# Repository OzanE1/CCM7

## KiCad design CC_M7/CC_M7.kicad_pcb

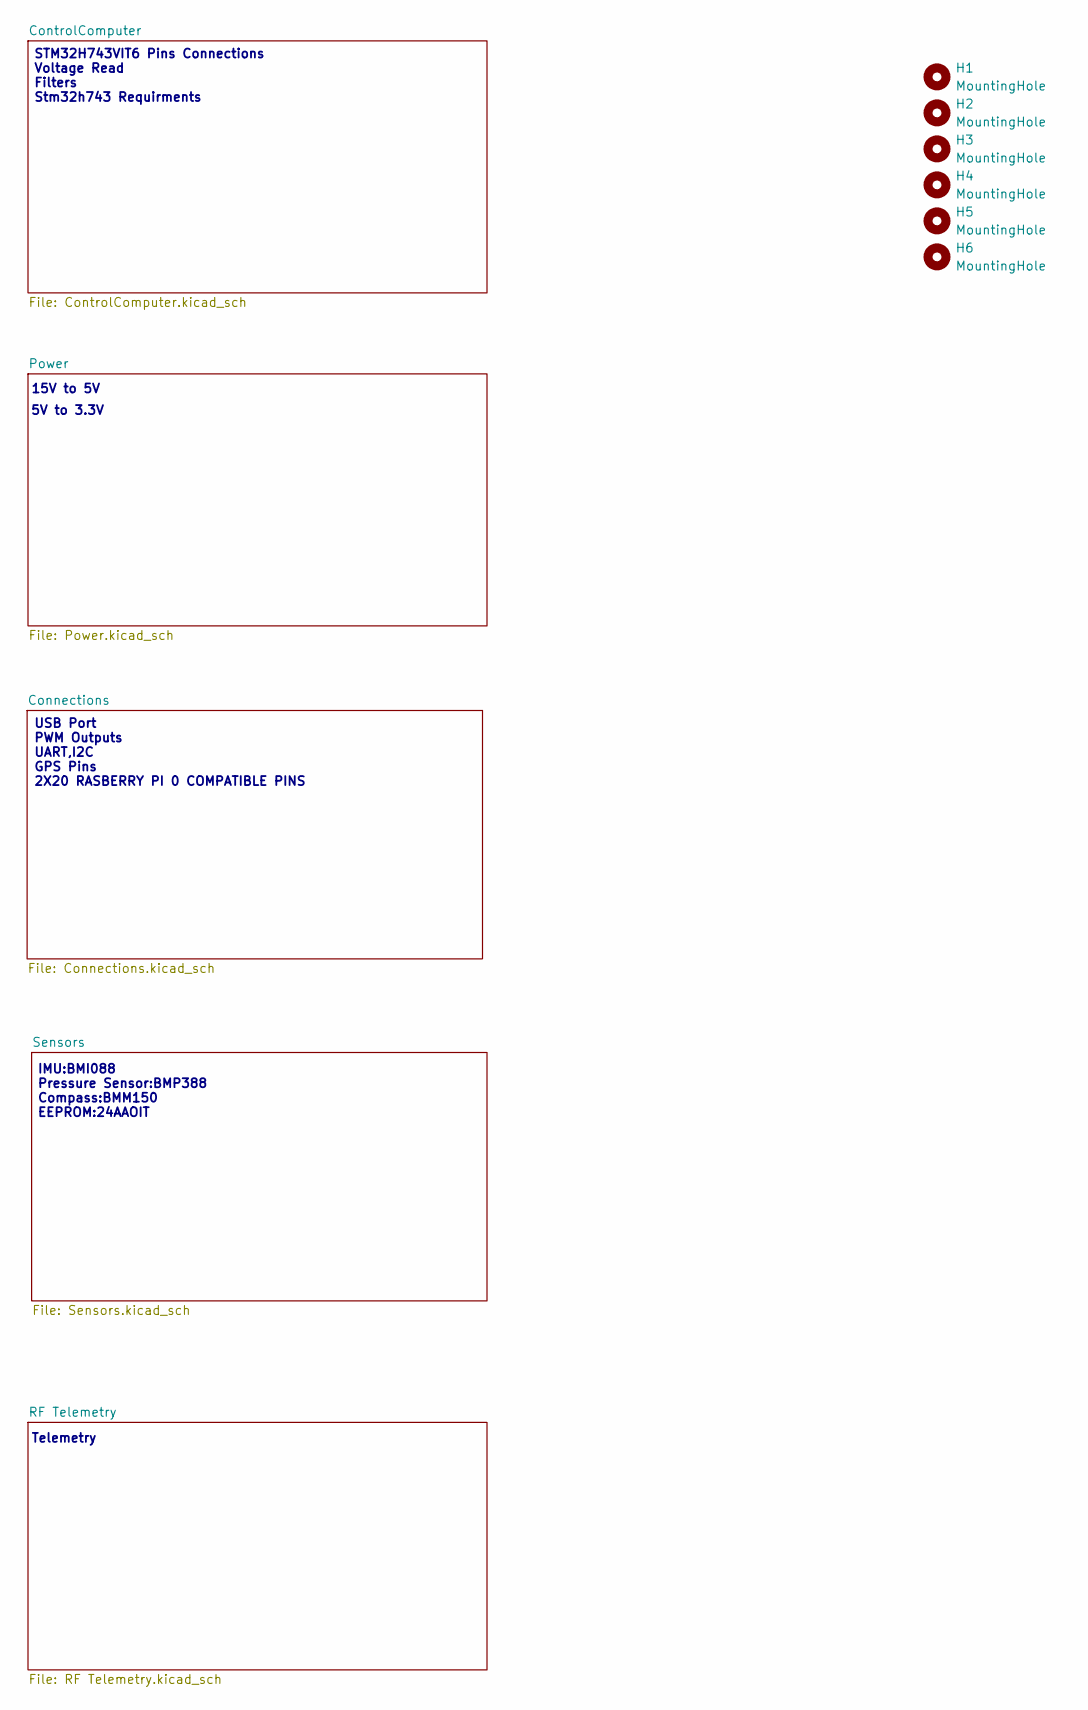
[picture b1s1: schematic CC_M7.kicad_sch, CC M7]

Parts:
H1, H2, H3, H4, H5, H6: MountingHole; MountingHole_3.2mm_M3_ISO14580_Pad

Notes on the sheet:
15V to 5V
5V to 3.3V
USB Port PWM Outputs UART,I2C GPS Pins 2X20 RASBERRY PI 0 COMPATIBLE PINS
Telemetry
STM32H743VIT6 Pins Connections Voltage Read Filters Stm32h743 Requirments
IMU:BMI088 Pressure Sensor:BMP388 Compass:BMM150 EEPROM:24AAOIT

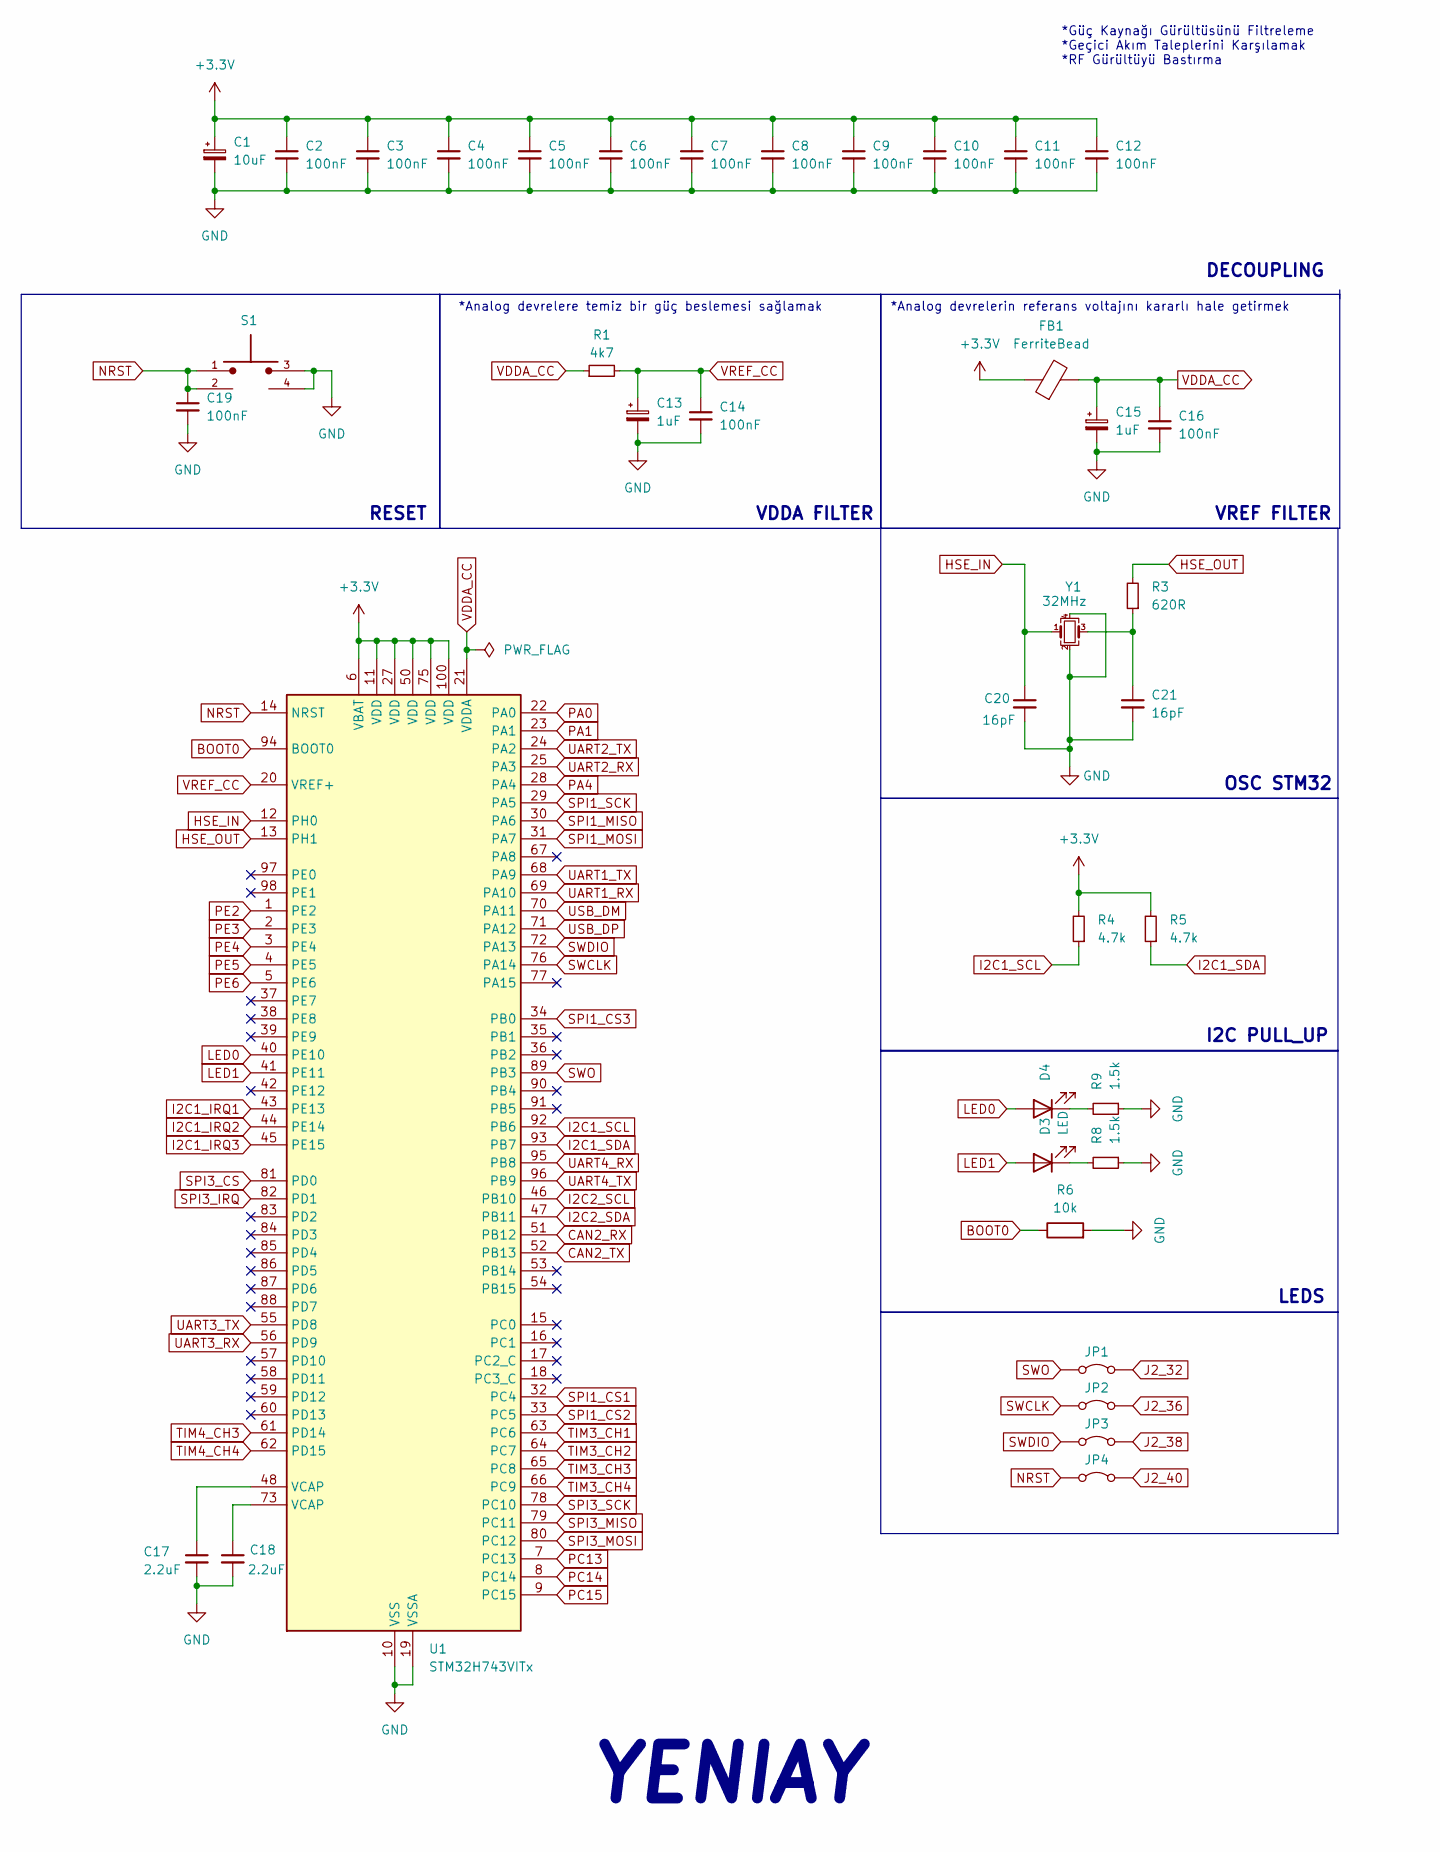
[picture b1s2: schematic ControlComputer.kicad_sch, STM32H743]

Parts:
C1: 10uF; C_0603_1608Metric
C2, C3, C4, C5, C6, C7, C8, C9, C10, C11, C12, C14, C16, C19: 100nF; C_0603_1608Metric
C13, C15: 1uF; C_0603_1608Metric
C17, C18: 2.2uF; C_0603_1608Metric
C20, C21: 16pF; C_0603_1608Metric
D3, D4: LED; LED_0603_1608Metric
FB1: FerriteBead; L_0603_1608Metric
JP1, JP2, JP3, JP4: SWDIO; jmpertest
R1: 4k7; R_0603_1608Metric
R3: 620R; R_0603_1608Metric
R4, R5: 4.7k; R_0603_1608Metric
R6: 10k; R_0603_1608Metric
R8, R9: 1.5k; R_0603_1608Metric
S1: SKRPABE010; SW_SKRPABE010
U1: STM32H743VITx; LQFP-100_14x14mm_P0.5mm
Y1: 32MHz; Crystal_SMD_3225-4Pin_3.2x2.5mm

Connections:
+3.3V: C1.1, C2.1, C3.1, C4.1, C5.1, C6.1, C7.1, C8.1, C9.1, C10.1, C11.1, C12.1, FB1.1, R4.2, R5.2, U1.6 (VBAT), U1.11 (VDD), U1.27 (VDD), U1.50 (VDD), U1.75 (VDD), U1.100 (VDD); also elsewhere on the board
BOOT0: R6.1, U1.94 (BOOT0)
CAN2_RX: U1.51 (PB12); also elsewhere on the board
CAN2_TX: U1.52 (PB13); also elsewhere on the board
GND: C1.2, C2.2, C3.2, C4.2, C5.2, C6.2, C7.2, C8.2, C9.2, C10.2, C11.2, C12.2, C13.2, C14.2, C15.2, C16.2, C17.2, C18.2, C19.2, C20.2, C21.2, R6.2, R8.1, R9.1, S1.3, S1.4, U1.10 (VSS), U1.19 (VSSA), U1.26 (VSS), U1.49 (VSS), U1.74 (VSS), U1.99 (VSS), Y1.2, Y1.4; also elsewhere on the board
HSE_IN: C20.1, U1.12 (PH0), Y1.1
HSE_OUT: R3.2, U1.13 (PH1)
I2C1_IRQ1: U1.43 (PE13); also elsewhere on the board
I2C1_IRQ2: U1.44 (PE14); also elsewhere on the board
I2C1_IRQ3: U1.45 (PE15); also elsewhere on the board
I2C1_SCL: R4.1, U1.92 (PB6); also elsewhere on the board
I2C1_SDA: R5.1, U1.93 (PB7); also elsewhere on the board
I2C2_SCL: U1.46 (PB10); also elsewhere on the board
I2C2_SDA: U1.47 (PB11); also elsewhere on the board
J2_32: JP1.2 (B); also elsewhere on the board
J2_36: JP2.2 (B); also elsewhere on the board
J2_38: JP3.2 (B); also elsewhere on the board
J2_40: JP4.2 (B); also elsewhere on the board
LED0: D4.2 (A), U1.40 (PE10)
LED1: D3.2 (A), U1.41 (PE11)
NRST: C19.1, JP4.1 (A), S1.1, S1.2, U1.14 (NRST)
unnamed: C17.1, U1.48 (VCAP)
unnamed: C18.1, U1.73 (VCAP)
unnamed: C21.1, R3.1, Y1.3
unnamed: D3.1 (K), R8.2
unnamed: D4.1 (K), R9.2
PA0: U1.22 (PA0); also elsewhere on the board
PA1: U1.23 (PA1); also elsewhere on the board
PA4: U1.28 (PA4); also elsewhere on the board
PC13: U1.7 (PC13); also elsewhere on the board
PC14: U1.8 (PC14); also elsewhere on the board
PC15: U1.9 (PC15); also elsewhere on the board
PE2: U1.1 (PE2); also elsewhere on the board
PE3: U1.2 (PE3); also elsewhere on the board
PE4: U1.3 (PE4); also elsewhere on the board
PE5: U1.4 (PE5); also elsewhere on the board
PE6: U1.5 (PE6); also elsewhere on the board
SPI1_CS1: U1.32 (PC4); also elsewhere on the board
SPI1_CS2: U1.33 (PC5); also elsewhere on the board
SPI1_CS3: U1.34 (PB0); also elsewhere on the board
SPI1_MISO: U1.30 (PA6); also elsewhere on the board
SPI1_MOSI: U1.31 (PA7); also elsewhere on the board
SPI1_SCK: U1.29 (PA5); also elsewhere on the board
SPI3_CS: U1.81 (PD0); also elsewhere on the board
SPI3_IRQ: U1.82 (PD1); also elsewhere on the board
SPI3_MISO: U1.79 (PC11); also elsewhere on the board
SPI3_MOSI: U1.80 (PC12); also elsewhere on the board
SPI3_SCK: U1.78 (PC10); also elsewhere on the board
SWCLK: JP2.1 (A), U1.76 (PA14)
SWDIO: JP3.1 (A), U1.72 (PA13)
SWO: JP1.1 (A), U1.89 (PB3)
TIM3_CH1: U1.63 (PC6); also elsewhere on the board
TIM3_CH2: U1.64 (PC7); also elsewhere on the board
TIM3_CH3: U1.65 (PC8); also elsewhere on the board
TIM3_CH4: U1.66 (PC9); also elsewhere on the board
TIM4_CH3: U1.61 (PD14); also elsewhere on the board
TIM4_CH4: U1.62 (PD15); also elsewhere on the board
UART1_RX: U1.69 (PA10); also elsewhere on the board
UART1_TX: U1.68 (PA9); also elsewhere on the board
UART2_RX: U1.25 (PA3); also elsewhere on the board
UART2_TX: U1.24 (PA2); also elsewhere on the board
UART3_RX: U1.56 (PD9); also elsewhere on the board
UART3_TX: U1.55 (PD8); also elsewhere on the board
UART4_RX: U1.95 (PB8); also elsewhere on the board
UART4_TX: U1.96 (PB9); also elsewhere on the board
USB_DM: U1.70 (PA11); also elsewhere on the board
USB_DP: U1.71 (PA12); also elsewhere on the board
VDDA_CC: C15.1, C16.1, FB1.2, R1.1, U1.21 (VDDA)
VREF_CC: C13.1, C14.1, R1.2, U1.20 (VREF+)

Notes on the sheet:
*Güç Kaynağı Gürültüsünü Filtreleme *Geçici Akım Taleplerini Karşılamak *RF Gürültüyü Bastırma
*Analog devrelere temiz bir güç beslemesi sağlamak
DECOUPLING
OSC STM32
VREF FILTER
RESET
I2C PULL_UP
*Analog devrelerin referans voltajını kararlı hale getirmek
LEDS
YENIAY
VDDA FILTER

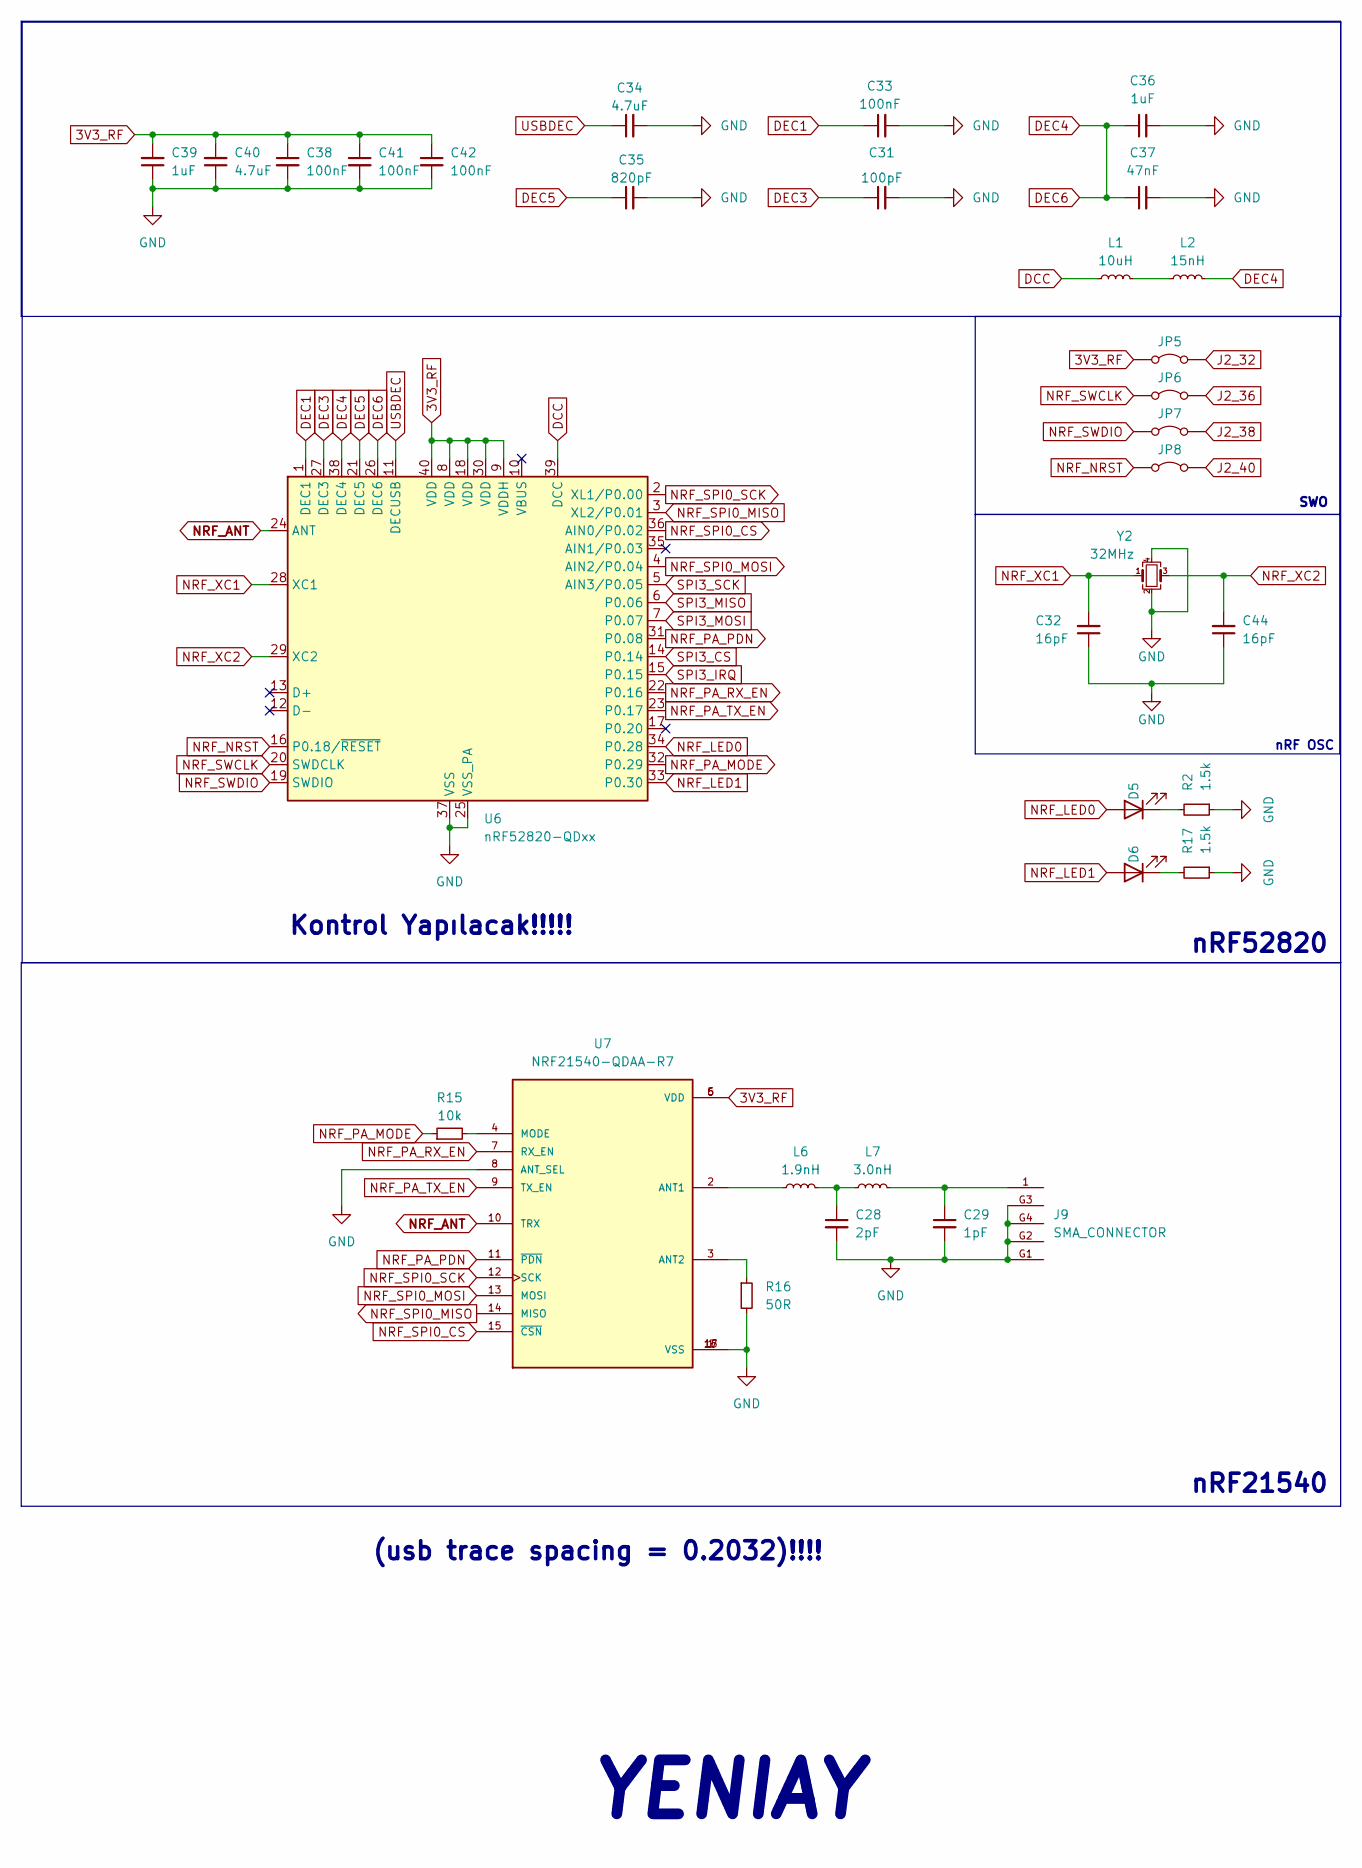
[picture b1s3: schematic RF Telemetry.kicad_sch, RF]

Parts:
C28: 2pF; C_0201_0603Metric
C29: 1pF; C_0201_0603Metric
C31: 100pF; C_0603_1608Metric
C32, C44: 16pF; C_0603_1608Metric
C33, C38, C41, C42: 100nF; C_0603_1608Metric
C34, C40: 4.7uF; C_0603_1608Metric
C35: 820pF; C_0603_1608Metric
C36, C39: 1uF; C_0603_1608Metric
C37: 47nF; C_0603_1608Metric
D5, D6: LED; LED_0603_1608Metric
J9: SMA_CONNECTOR; LPRS_SMA_CONNECTOR; PARTREV 1.3
JP5, JP6, JP7, JP8: SWDIO; jmpertest
L1: 10uH; L_0603_1608Metric
L2: 15nH; L_0603_1608Metric
L6: 1.9nH; L_0201_0603Metric
L7: 3.0nH; L_0201_0603Metric
R2, R17: 1.5k; R_0603_1608Metric
R15: 10k; R_0603_1608Metric
R16: 50R; R_0603_1608Metric
U6: nRF52820-QDxx; QFN-40-1EP_5x5mm_P0.4mm_EP3.6x3.6mm
U7: NRF21540-QDAA-R7; QFN65P400X400X95-17N; PARTREV 1.0
Y2: 32MHz; Crystal_SMD_3225-4Pin_3.2x2.5mm

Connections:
3V3_RF: C38.1, C39.2, C40.2, C41.1, C42.1, JP5.1 (A), U6.8 (VDD), U6.9 (VDDH), U6.18 (VDD), U6.30 (VDD), U6.40 (VDD), U7.5 (VDD), U7.6 (VDD); also elsewhere on the board
DCC: L1.1, U6.39 (DCC)
DEC1: C33.1, U6.1 (DEC1)
DEC3: C31.1, U6.27 (DEC3)
DEC4: C36.1, C37.1, L2.2, U6.26 (DEC6), U6.38 (DEC4)
DEC5: C35.1, U6.21 (DEC5)
GND: C28.2, C29.2, C31.2, C32.1, C33.2, C34.2, C35.2, C36.2, C37.2, C38.2, C39.1, C40.1, C41.2, C42.2, C44.1, J9.G1, J9.G2, J9.G3, J9.G4, R2.1, R16.2, R17.1, U6.25 (VSS_PA), U6.37 (VSS), U6.41 (VSS), U7.1 (VSS), U7.8 (ANT_SEL), U7.16 (VSS), U7.17 (VSS), Y2.2, Y2.4; also elsewhere on the board
J2_32: JP5.2 (B); also elsewhere on the board
J2_36: JP6.2 (B); also elsewhere on the board
J2_38: JP7.2 (B); also elsewhere on the board
J2_40: JP8.2 (B); also elsewhere on the board
NRF_ANT: U6.24 (ANT), U7.10 (TRX)
NRF_LED0: D5.2 (A), U6.34 (P0.28)
NRF_LED1: D6.2 (A), U6.33 (P0.30)
NRF_NRST: JP8.1 (A), U6.16 (P0.18/~RESET)
NRF_PA_MODE: R15.1, U6.32 (P0.29)
NRF_PA_PDN: U6.31 (P0.08), U7.11 (~PDN)
NRF_PA_RX_EN: U6.22 (P0.16), U7.7 (RX_EN)
NRF_PA_TX_EN: U6.23 (P0.17), U7.9 (TX_EN)
NRF_SPI0_CS: U6.36 (AIN0/P0.02), U7.15 (~CSN)
NRF_SPI0_MISO: U6.3 (XL2/P0.01), U7.14 (MISO)
NRF_SPI0_MOSI: U6.4 (AIN2/P0.04), U7.13 (MOSI)
NRF_SPI0_SCK: U6.2 (XL1/P0.00), U7.12 (SCK)
NRF_SWCLK: JP6.1 (A), U6.20 (SWDCLK)
NRF_SWDIO: JP7.1 (A), U6.19 (SWDIO)
NRF_XC1: C32.2, U6.28 (XC1), Y2.1
NRF_XC2: C44.2, U6.29 (XC2), Y2.3
unnamed: C28.1, L6.2, L7.1
unnamed: C29.1, J9.1, L7.2
unnamed: D5.1 (K), R2.2
unnamed: D6.1 (K), R17.2
unnamed: L1.2, L2.1
unnamed: L6.1, U7.2 (ANT1)
unnamed: R16.1, U7.3 (ANT2)
unnamed: R15.2, U7.4 (MODE)
SPI3_CS: U6.14 (P0.14); also elsewhere on the board
SPI3_IRQ: U6.15 (P0.15); also elsewhere on the board
SPI3_MISO: U6.6 (P0.06); also elsewhere on the board
SPI3_MOSI: U6.7 (P0.07); also elsewhere on the board
SPI3_SCK: U6.5 (AIN3/P0.05); also elsewhere on the board
USBDEC: C34.1, U6.11 (DECUSB)

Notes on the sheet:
Kontrol Yapılacak!!!!!
(usb trace spacing = 0.2032)!!!!
nRF21540
nRF52820
YENIAY
nRF OSC
SWO

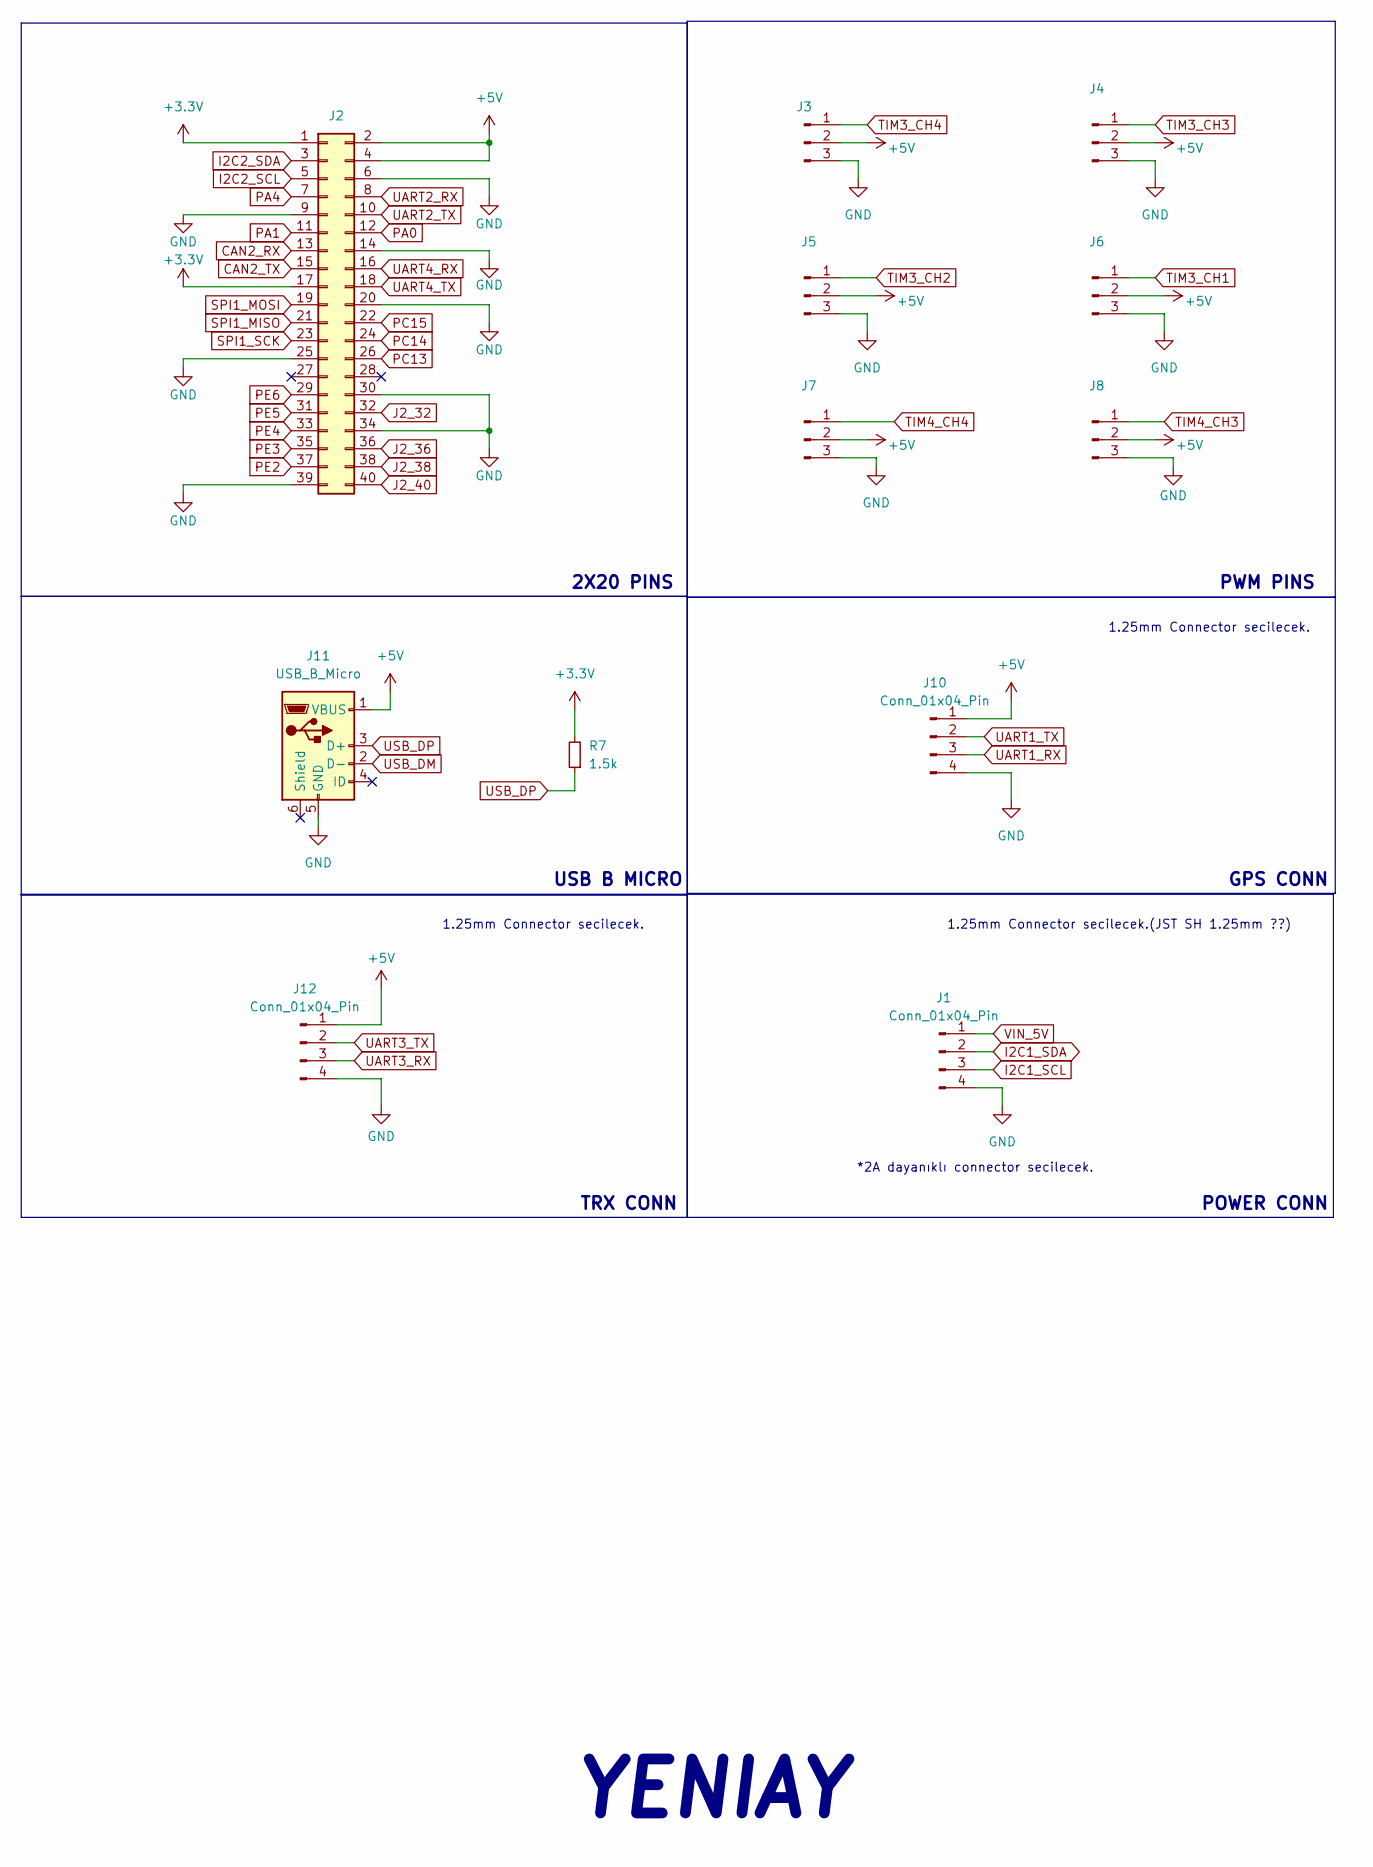
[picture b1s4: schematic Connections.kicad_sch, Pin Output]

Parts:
J1, J10, J12: Conn_01x04_Pin; Hirose_DF13-04P-1.25DSA_1x04_P1.25mm_Vertical
J2: IDC-Header_2x20_P2.54mm_Vertical
J3, J4, J5, J6, J7, J8: Conn_01x03_Pin; 1x03_2.54vertical
J11: USB_B_Micro; USB_Micro-B_Wuerth_629105150521
R7: 1.5k; R_0603_1608Metric

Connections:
+3.3V: J2.1, J2.17, R7.2; also elsewhere on the board
+5V: J2.2, J2.4, J3.2, J4.2, J5.2, J6.2, J7.2, J8.2, J10.1, J11.1 (VBUS), J12.1; also elsewhere on the board
CAN2_RX: J2.13; also elsewhere on the board
CAN2_TX: J2.15; also elsewhere on the board
GND: J1.4, J2.6, J2.9, J2.14, J2.20, J2.25, J2.30, J2.34, J2.39, J3.3, J4.3, J5.3, J6.3, J7.3, J8.3, J10.4, J11.5 (GND), J12.4; also elsewhere on the board
I2C1_SCL: J1.3; also elsewhere on the board
I2C1_SDA: J1.2; also elsewhere on the board
I2C2_SCL: J2.5; also elsewhere on the board
I2C2_SDA: J2.3; also elsewhere on the board
J2_32: J2.32; also elsewhere on the board
J2_36: J2.36; also elsewhere on the board
J2_38: J2.38; also elsewhere on the board
J2_40: J2.40; also elsewhere on the board
PA0: J2.12; also elsewhere on the board
PA1: J2.11; also elsewhere on the board
PA4: J2.7; also elsewhere on the board
PC13: J2.26; also elsewhere on the board
PC14: J2.24; also elsewhere on the board
PC15: J2.22; also elsewhere on the board
PE2: J2.37; also elsewhere on the board
PE3: J2.35; also elsewhere on the board
PE4: J2.33; also elsewhere on the board
PE5: J2.31; also elsewhere on the board
PE6: J2.29; also elsewhere on the board
SPI1_MISO: J2.21; also elsewhere on the board
SPI1_MOSI: J2.19; also elsewhere on the board
SPI1_SCK: J2.23; also elsewhere on the board
TIM3_CH1: J6.1; also elsewhere on the board
TIM3_CH2: J5.1; also elsewhere on the board
TIM3_CH3: J4.1; also elsewhere on the board
TIM3_CH4: J3.1; also elsewhere on the board
TIM4_CH3: J8.1; also elsewhere on the board
TIM4_CH4: J7.1; also elsewhere on the board
UART1_RX: J10.3; also elsewhere on the board
UART1_TX: J10.2; also elsewhere on the board
UART2_RX: J2.8; also elsewhere on the board
UART2_TX: J2.10; also elsewhere on the board
UART3_RX: J12.3; also elsewhere on the board
UART3_TX: J12.2; also elsewhere on the board
UART4_RX: J2.16; also elsewhere on the board
UART4_TX: J2.18; also elsewhere on the board
USB_DM: J11.2 (D-); also elsewhere on the board
USB_DP: J11.3 (D+), R7.1; also elsewhere on the board
VIN_5V: J1.1; also elsewhere on the board

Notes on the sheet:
YENIAY
POWER CONN
PWM PINS
GPS CONN
1.25mm Connector secilecek.
*2A dayanıklı connector secilecek.
TRX CONN
2X20 PINS
1.25mm Connector secilecek.(JST SH 1.25mm ??)
USB B MICRO

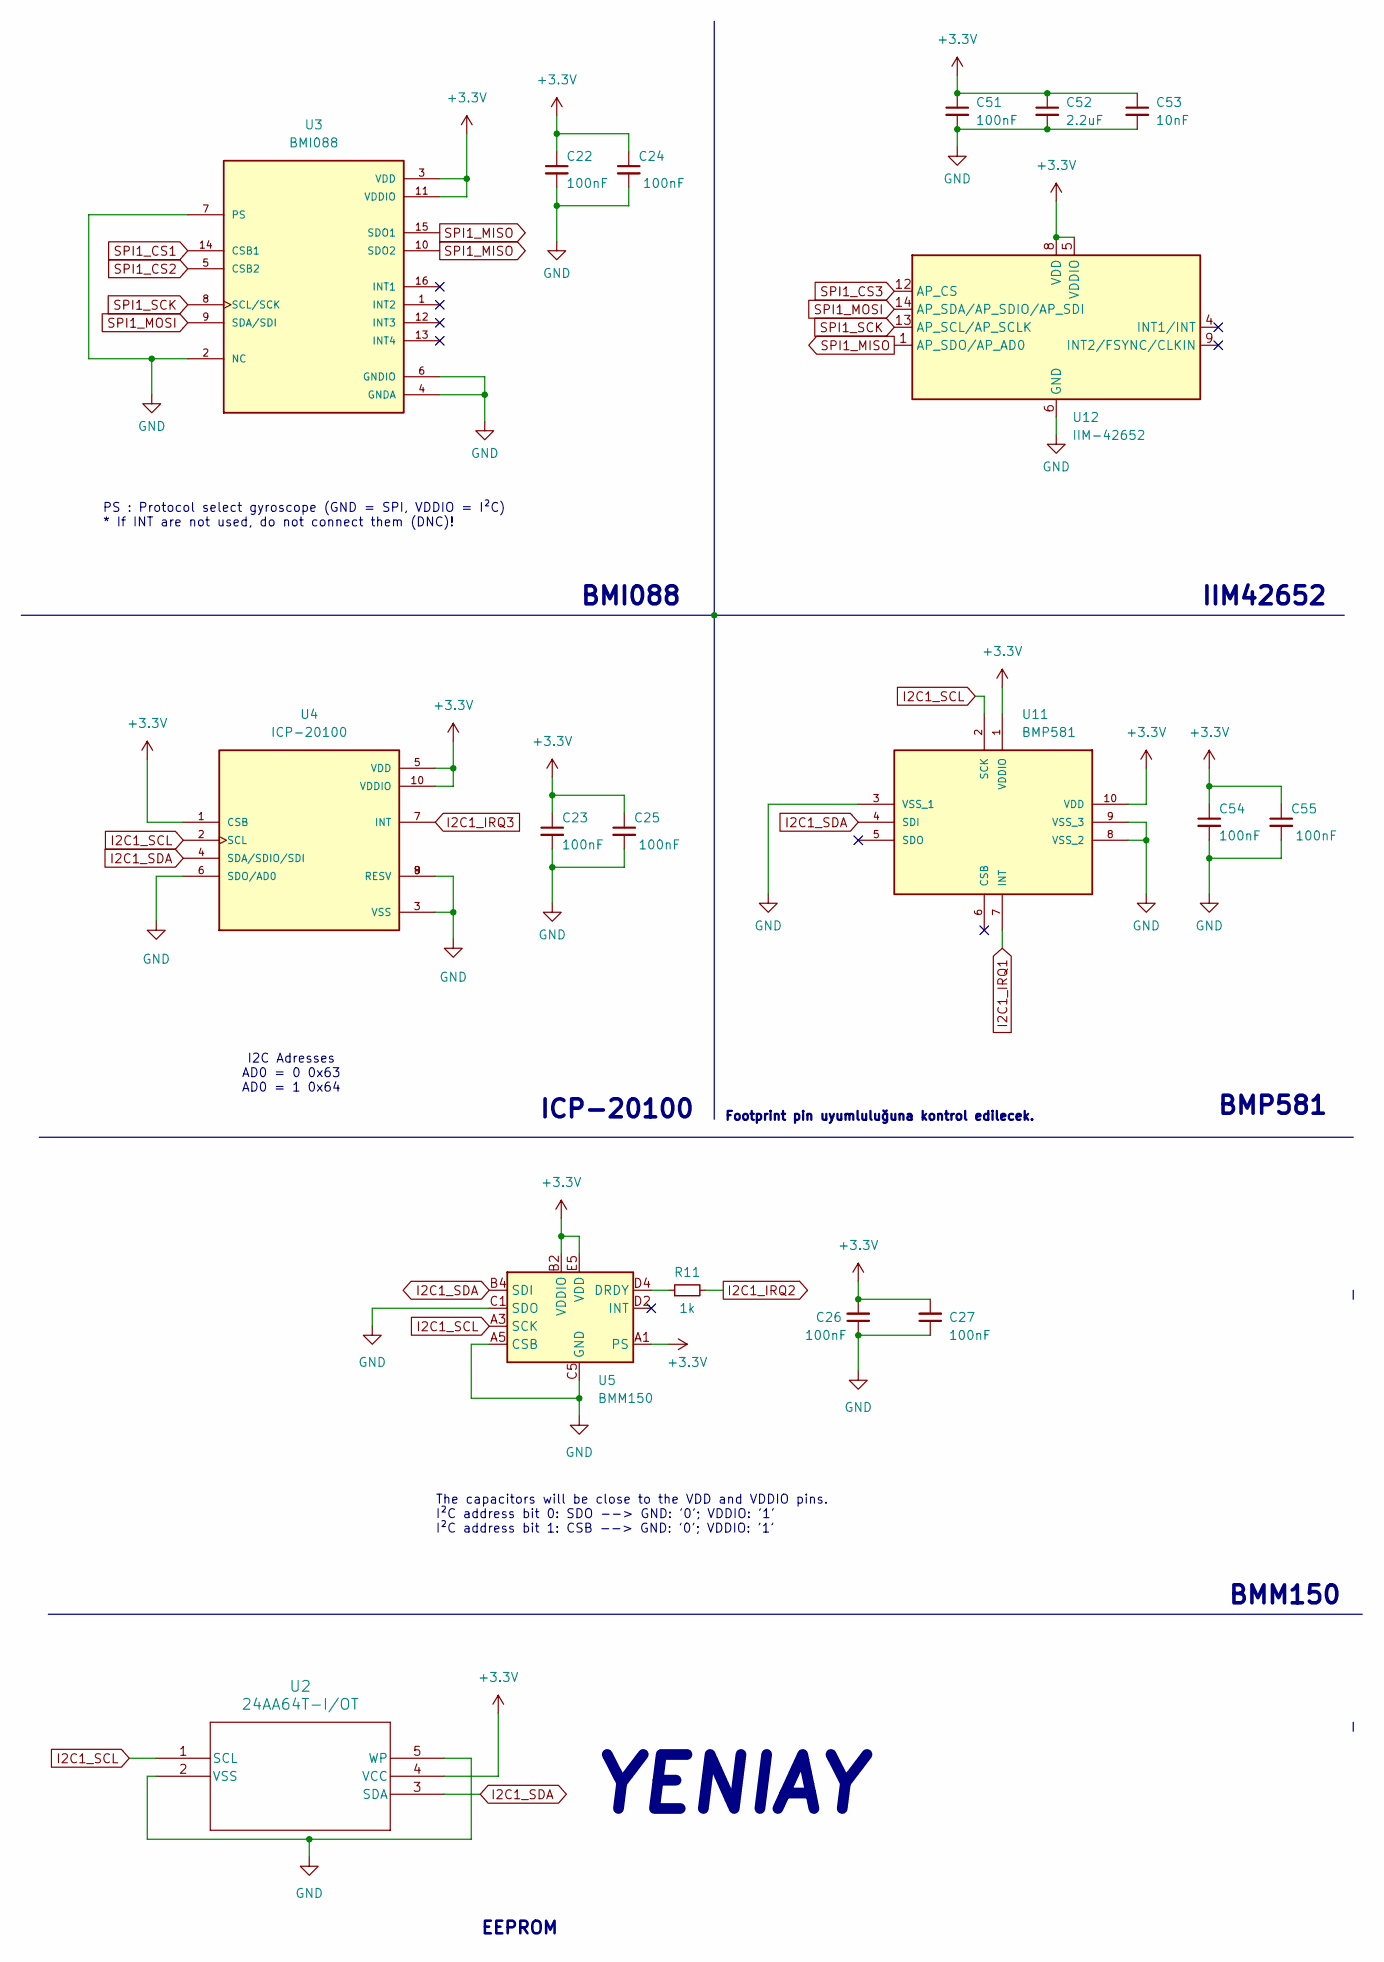
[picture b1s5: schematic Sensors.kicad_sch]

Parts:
C22, C23, C24, C25, C26, C27, C51, C54, C55: 100nF; C_0603_1608Metric
C52: 2.2uF; C_0603_1608Metric
C53: 10nF; C_0603_1608Metric
R11: 1k; R_0603_1608Metric
U2: 24AA64T-I/OT; SOT-23-5_HandSoldering
U3: BMI088; PQFN50P450X300X100-16N
U4: ICP-20100; PQFN50P200X200X85-10N; PARTREV 1.1
U5: BMM150; WLCSP-12_1.56x1.56mm_P0.4mm
U11: BMP581; Manufacturer_Part_Number BMP581
U12: IIM-42652; Bosch_LGA-14_3x2.5mm_P0.5mm

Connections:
+3.3V: C22.1, C23.1, C24.1, C25.1, C26.2, C27.2, C51.1, C52.1, C53.1, C54.1, C55.1, U2.4 (VCC), U3.3 (VDD), U3.11 (VDDIO), U4.1 (CSB), U4.5 (VDD), U4.10 (VDDIO), U5.A1 (PS), U5.B2 (VDDIO), U5.E5 (VDD), U11.1 (VDDIO), U11.10 (VDD), U12.5 (VDDIO), U12.8 (VDD); also elsewhere on the board
GND: C22.2, C23.2, C24.2, C25.2, C26.1, C27.1, C51.2, C52.2, C53.2, C54.2, C55.2, U2.2 (VSS), U2.5 (WP), U3.2 (NC), U3.4 (GNDA), U3.6 (GNDIO), U3.7 (PS), U4.3 (VSS), U4.6 (SDO/AD0), U4.8 (RESV), U4.9 (RESV), U5.A5 (CSB), U5.C1 (SDO), U5.C5 (GND), U5.E1 (GND), U5.E3 (GND), U11.3 (VSS_1), U11.8 (VSS_2), U11.9 (VSS_3), U12.6 (GND), U12.7 (GND); also elsewhere on the board
I2C1_IRQ1: U11.7 (INT); also elsewhere on the board
I2C1_IRQ2: R11.2; also elsewhere on the board
I2C1_IRQ3: U4.7 (INT); also elsewhere on the board
I2C1_SCL: U2.1 (SCL), U4.2 (SCL), U5.A3 (SCK), U11.2 (SCK); also elsewhere on the board
I2C1_SDA: U2.3 (SDA), U4.4 (SDA/SDIO/SDI), U5.B4 (SDI), U11.4 (SDI); also elsewhere on the board
unnamed: R11.1, U5.D4 (DRDY)
SPI1_CS1: U3.14 (CSB1); also elsewhere on the board
SPI1_CS2: U3.5 (CSB2); also elsewhere on the board
SPI1_CS3: U12.12 (AP_CS); also elsewhere on the board
SPI1_MISO: U3.10 (SDO2), U3.15 (SDO1), U12.1 (AP_SDO/AP_AD0); also elsewhere on the board
SPI1_MOSI: U3.9 (SDA/SDI), U12.14 (AP_SDA/AP_SDIO/AP_SDI); also elsewhere on the board
SPI1_SCK: U3.8 (SCL/SCK), U12.13 (AP_SCL/AP_SCLK); also elsewhere on the board

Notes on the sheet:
YENIAY
BMP581
IIM42652
The capacitors will be close to the VDD and VDDIO pins. I²C address bit 0: SDO --> GND: '0'; VDDIO: '1' I²C address bit 1: CSB --> GND: '0'; VDDIO: '1'
Footprint pin uyumluluğuna kontrol edilecek.
BMM150
ICP-20100
I2C Adresses AD0 = 0 0x63 AD0 = 1 0x64
EEPROM
PS : Protocol select gyroscope (GND = SPI, VDDIO = I²C) * If INT are not used, do not connect them (DNC)!
BMI088

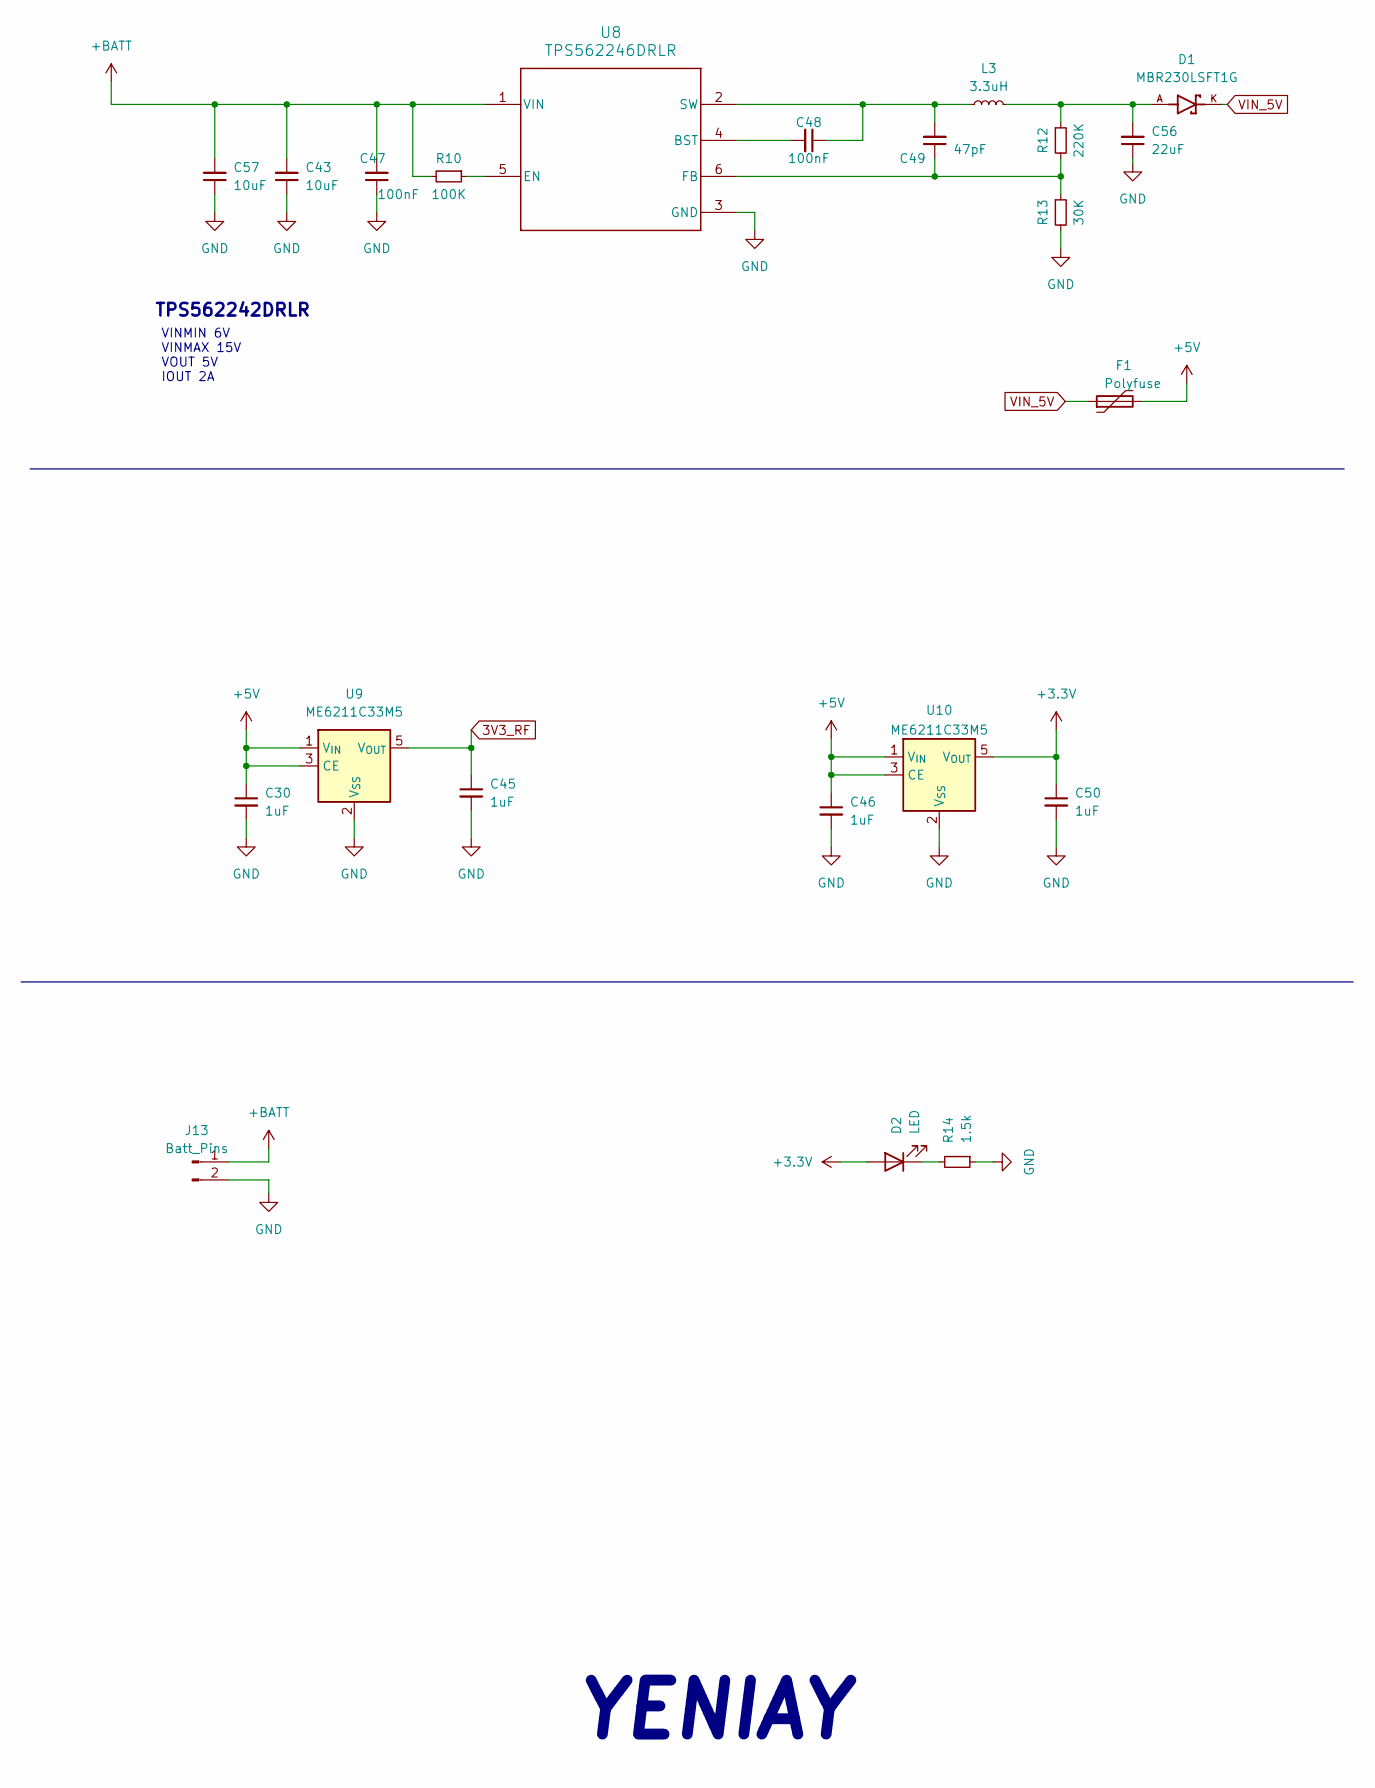
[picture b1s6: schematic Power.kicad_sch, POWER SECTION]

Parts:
C30, C45, C46, C50: 1uF; C_0805_2012Metric
C43, C57: 10uF; C_1206_3216Metric
C47: 100nF; C_1206_3216Metric
C48: 100nF; C_0603_1608Metric
C49: 47pF; C_0603_1608Metric
C56: 22uF; C_0805_2012Metric
D1: MBR230LSFT1G; SODFL3619X98N; PARTREV 1
D2: LED; LED_0603_1608Metric
F1: Polyfuse; Fuse_1206_3216Metric
J13: Batt_Pins; PinSocket_1x02_P2.54mm_Vertical
L3: 3.3uH; L_Changjiang_FXL0650
R10: 100K; R_0603_1608Metric
R12: 220K; R_0603_1608Metric
R13: 30K; R_0603_1608Metric
R14: 1.5k; R_0603_1608Metric
U8: TPS562246DRLR; DRL0006A-MFG
U9, U10: ME6211C33M5; SOT-23-5

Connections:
3V3_RF: C45.1, U9.5 (V_{OUT}); also elsewhere on the board
+3.3V: C50.1, D2.2 (A), U10.5 (V_{OUT}); also elsewhere on the board
+5V: C30.1, C46.1, F1.2, U9.1 (V_{IN}), U9.3 (CE), U10.1 (V_{IN}), U10.3 (CE); also elsewhere on the board
+BATT: C43.2, C47.2, C57.2, J13.1, R10.2, U8.1 (VIN)
GND: C30.2, C43.1, C45.2, C46.2, C47.1, C50.2, C56.1, C57.1, J13.2, R13.2, R14.1, U8.3 (GND), U9.2 (V_{SS}), U10.2 (V_{SS}); also elsewhere on the board
unnamed: C56.2, D1.A, L3.2, R12.1
unnamed: D2.1 (K), R14.2
unnamed: C48.2, U8.4 (BST)
unnamed: R10.1, U8.5 (EN)
unnamed: C49.1, R12.2, R13.1, U8.6 (FB)
unnamed: C48.1, C49.2, L3.1, U8.2 (SW)
VIN_5V: D1.K, F1.1; also elsewhere on the board

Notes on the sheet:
YENIAY
VINMIN 6V VINMAX 15V VOUT 5V IOUT 2A
TPS562242DRLR
